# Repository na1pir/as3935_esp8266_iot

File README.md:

# Thunderstorm sensor protected iot switch
*Another a bit more complex project written in c with espressif sdk for my diploma thesis, so it is in prototype stage and work in progress when I have time to work on it . . .*

Copyright (c) 2015 Uroš Golob <golob.uros@gmail.com> 
 
Work was done with intention to protect electronic devices and so lower e-waste.
It might work or it may not, just don't sue me if your house burns down or if it kills you...

This software and hardware is described in my diploma thesis(work in progress). 
   
Use it for *personal* use as you wish, just keep this notice on it if you do! 
And return changes back free of charge by same restrictions and notice! 

This software uses espressif sdk software, spi library from David Ogilvy(MetalPhreak) and libesphttpd & wifi settins form Jeroen Domburg(sprite_fm). So use and rescpect their respective licencies for their work. 

Development took alot of time and money so remember me with some spare 
bitcoins: 1MaGphnuiMjywjQPKHKF239wzcef4KpNxX if you wish:)

For comercial use you can contact me and we can make some separate licencing deal...

## What it is?
Well this thing uses some crazy trickery from ams... and lovely soc from espressif... 
OK as3935 is (well not so simple) chip that uses LC antenna tuned to 500khz to detect lightning discharges.
It measures amplitude and uses some crazy statistics to determine distance from face of the thunderstorm. And gladly ignores man made discharges.
Well I added a bit of trickery of my own to libesphttpd and used spi driver to talk to as3935 with esp8266.
When you mix everything together add couple of passives, transistor, optotransistor and relays you got a switch that disengages relay when it detect nearby thunderstorm. 

This is my baby and so work in progress and maybe never ending rolling release... 

Well you can order boards from [DirtyPCB's] 
(http://dirtypcbs.com/view.php?share=10417&accesskey=882ad84b962361d538d1656b4bbab783)

## bom: 
 * esp-201 or esp12 or esp12e
 * as3935
 * ma5532
 * ams1117 3.3
 * optotransistors
 * npns
 * couple of R, C & D 
 * pair of relays

## how to:
1. get yourself working esp-open-sdk + newer sdk from espressif and link it to esp-open-sdk/sdk 
2. additionally get working sprite_fm libesphttpd and cats/led example so you can check and update any changes... 
3. find spi driver from MetalPhreak and check that example

 * I should add everything as git sub-modules, but as of now I don't know how...

 * make sure to export your esp-open-sdk/xtensa-lx106-elf/bin path to system path... additionally export esp-open-sdk/sdk as SDK_BASE, then ESPTOOL... in ubuntu it is best to do it in .profile  

4. from as3935_esp8266_iot folder run

	**make clean all**

5. put esp into boot mode (i have reset and boot(rst and gpio0 respectively to gnd) buttons soldered into my board) so press reset and boot then lift reset first then boot and run

	**make burn** 
or 
	**sudo make burn** 
if your dial-out permission thingy stuffs aren't setup properly

6. for debbuging

	**make tty**

7. setup geany for above commands it will save you lots of time

*todo: fix all issues*

## user interface looks like this: 
![settings web page]
(https://github.com/na1pir/as3935_esp8266_iot/raw/master/webpage.png)

Text for thesis is available at https://dk.um.si/Dokument.php?id=99783&lang=eng
It is in Slovene language but generaly you can still look at pictures.

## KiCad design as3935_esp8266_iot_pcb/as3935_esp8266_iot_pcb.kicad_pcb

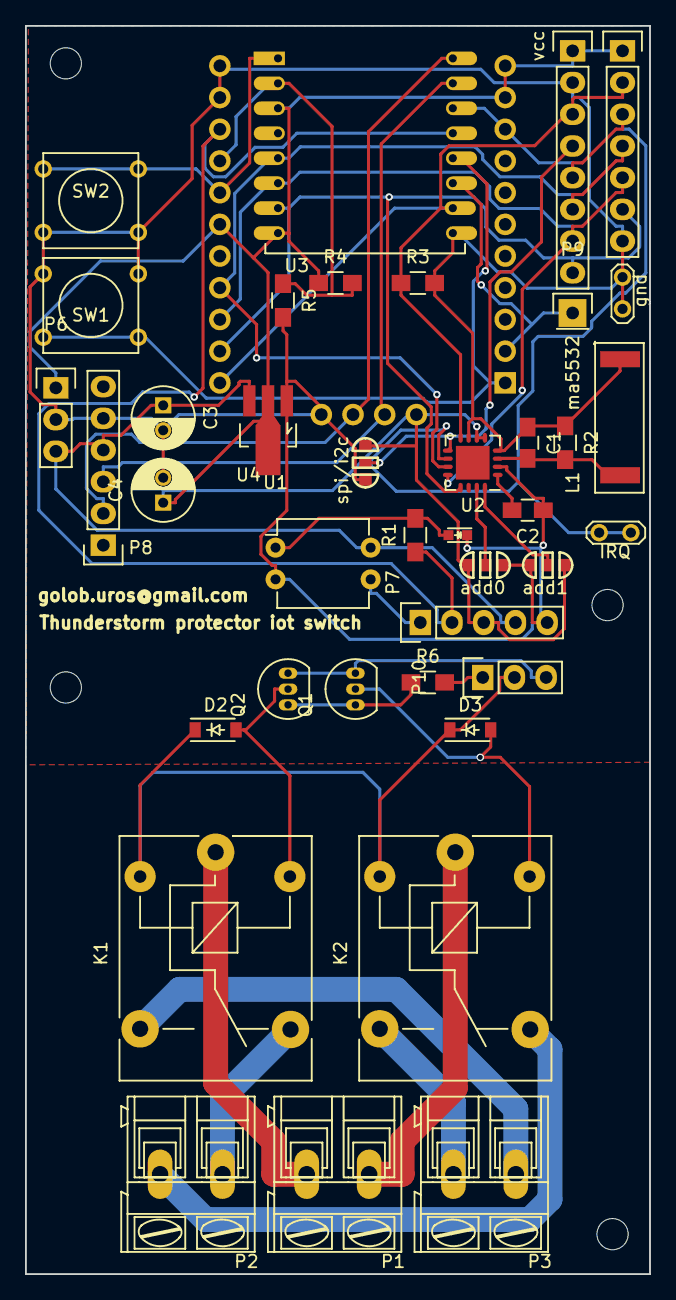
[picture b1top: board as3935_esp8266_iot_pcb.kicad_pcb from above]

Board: 2 copper layers, 50.0 x 100.0 mm, 44 parts (0 on the bottom side), 31 nets.

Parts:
C1, C2: C; C_0805_HandSoldering
C3, C4: C; C_Radial_D5_L11_P2
D1: LED; LED-0603
D2, D3: D; SOD-123
IRQ: TEST; TESTPOINT
K1, K2: RELAY_2RT; relay
L1: ma5532
P1, P2, P3: CONN_01X02; AK300-2
P5: CONN_01X07; Pin_Header_Straight_1x07
P6, P10: CONN_01X03; Pin_Header_Straight_1x03
P7: CONN_01X05; Pin_Header_Straight_1x05
P8: CONN_01X06; Pin_Header_Straight_1x06
P9: CONN_01X01; Pin_Header_Straight_1x01
Q1, Q2: Q_NPN_BCE; TO-92_Inline_Narrow_Oval
R1, R2, R3, R4, R5, R6: R; R_0805_HandSoldering
REF1, REF2, REF3, REF4: MountingHole_2-5mm
SW1: SW_FLASH; SW_PUSH_SMALL
SW2: SW_RESET; SW_PUSH_SMALL
U1: PC817; DIP-4_W7.62mm
U2: as3935; UQFN-16-1EP_4x4mm_Pitch0.65mm
U3: ESP-12
U4: ESP-201
U5: AP1117D33; SOT89-3_Housing_Handsoldering
add0, add1: JUMPER3; sj3
gnd: TEST; TESTPOINT
spi/i2c: JUMPER3; sj3
vcc: CONN_01X08; Pin_Header_Straight_1x08

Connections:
+3V3: C4.1, P5.1, P6.1, P7.3, R4.1, U2.5, U2.6, U3.3, U3.8, U4.10, U4.11, U4.17, U4.26, U5.2, add0.1, add1.1, spi/i2c.1, vcc.1
+5V: C3.1, D2.1, D3.1, K1.8, K2.8, P6.3, P7.4, P8.4, P10.2, U1.4, U5.3
/adc: R4.2, R5.1, U3.2, U4.15
/add0: U2.15, add0.2
/add1: U2.16, add1.2
/clk: P5.4, U2.11, U3.5, U4.19, vcc.6
/cs: P5.2, R3.1, U2.8, U3.10, U4.22, vcc.3
/flash: SW1.1, U3.12, U4.1
/irq: IRQ.1, P5.3, U2.10, U3.14, U4.9, vcc.5
/miso: P5.5, U2.12, U3.6, U4.20, vcc.7
/mosi: P5.6, U2.13, U3.7, U4.21, vcc.8
/reset: SW2.1, U3.1, U4.16
/rx: P8.3, U3.15, U4.25
/si: U2.9, spi/i2c.2, vcc.4
/to_sw: P7.2, R1.1, U3.13, U4.14
/to_switch: P7.1, P10.1, R6.2, U1.3
/tx: P8.2, U3.16, U4.24
GND: C1.1, C2.1, C3.2, C4.2, D1.1, L1.1, P5.7, P6.2, P7.5, P8.5, P10.3, Q1.3, Q2.3, R2.1, R3.2, R5.2, SW1.2, SW2.2, U1.2, U2.2, U2.4, U2.7, U3.9, U4.12, U4.13, U4.23, U5.1, add0.3, add1.3, gnd.1, spi/i2c.3, vcc.2
unnamed: C1.2, L1.2, R2.2, U2.3
unnamed: C2.2, U2.1
unnamed: D1.2, R1.2, U1.1
unnamed: D2.2, K1.9, Q2.2
unnamed: D3.2, K2.9, Q1.2
unnamed: K1.1, P2.1
unnamed: K1.3, P3.1
unnamed: K1.5, P1.2
unnamed: K2.1, P2.2
unnamed: K2.3, P3.2
unnamed: K2.5, P1.1
unnamed: P9.1, U3.11, U4.2
unnamed: Q1.1, Q2.1, R6.1

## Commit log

2015-07-06 initial commit it works a bit i guess but waiting for storm to test it... todo: distance probably not corect in this version find a flaw and fix it!!! todo: check if calibration actualy outputs anyth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
2015-07-06 readme file
2015-07-07 bunch of changes but still doesn't work todo: -irq won't fire -spi is still no go
2015-07-09 just random schanges... nothing important actualy
2015-07-09 alternative to interrupts
2015-07-11 a bit of explanation to readme
2015-07-11 adding 2 datasheets for both chips
2015-07-11 make
2015-07-11 changing spi clock based on http://www.esp8266.com/viewtopic.php?f=13&t=2367
2015-07-11 BIG RED FAIL BUTTON;"Whaaaaak whaaaak wahaak whak!" why oh why didn't i try that before as3935 structure registers were back to front, now everithing shuld be better:)
2015-07-11 updated todo's
2015-07-11 addig yet more datasheets
2015-07-11 there is something wrong with tun_cap
2015-07-12 bug in as3935 structure(now we have functional calibration mode) todo: tuncap unable to set odd numbers interrupts won't fire
2015-07-13 noise floor is calculated based on setting of noise floor and AFE and shown in μVrms
2015-07-13 removed todos just look into github issues
2015-07-26 adding couple of pictures and few small changes in code so everithing works withouth interrupts
2015-07-27 added srej settings in webpage dog probably ate missing ones:)
2015-07-27 another missing setting
2015-07-28 only smal spelling mistake
2015-07-29 comments remove
2015-07-30 added basic support for save settings all saved settings are loaded at boot time
2015-07-30 added label to save and ignored load settings if no data is in flash
2015-07-30 changed label for clearing statistics
2015-07-30 added reset to defoult for as3935
2015-07-30 just shufeling things around
2015-08-02 tried to add submodule but faild, well it is at least updated
2015-08-11 possible fix for spi communication needs some more testing but i think that it works:)
2015-08-12 first pcb rototype it can carry esp-201 or esp-12, as3935 chip with ma5532-ae coil antenna or module mop-1016 from www.embeddedadventures.com or as3935 lightning sensor module from playingwithfusion.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
2015-08-12 just simbols
2015-08-12 copper fill
2015-08-12 copper fill, smd transistor, resistors and capacitors on universal pads for smd 805 or trough hole
2015-08-12 gerbers
2015-08-18 new layout, added second transistor for relay,... digital side of pcb cal drive any relay board from ebay or something
2015-08-19 small redesign
2015-08-26 added simple pcb containing only digital part with sensor and microcontroler module with embedded wifi you'll have to add your own relays
2015-08-26 for page
2015-08-26 Create gh-pages branch via GitHub
2015-08-27 readme
    just like in webpage
2015-08-31 just re draft for diploma
2015-09-05 couple quirks
2015-09-12 well actualy that should have been pico farads not micro farads ups my bad...
2015-12-30 small printf
2015-12-30 just small changes
2017-02-14 Update README.md
    well it is not not working, it works perfectly well.
2017-02-14 Set theme jekyll-theme-hacker
